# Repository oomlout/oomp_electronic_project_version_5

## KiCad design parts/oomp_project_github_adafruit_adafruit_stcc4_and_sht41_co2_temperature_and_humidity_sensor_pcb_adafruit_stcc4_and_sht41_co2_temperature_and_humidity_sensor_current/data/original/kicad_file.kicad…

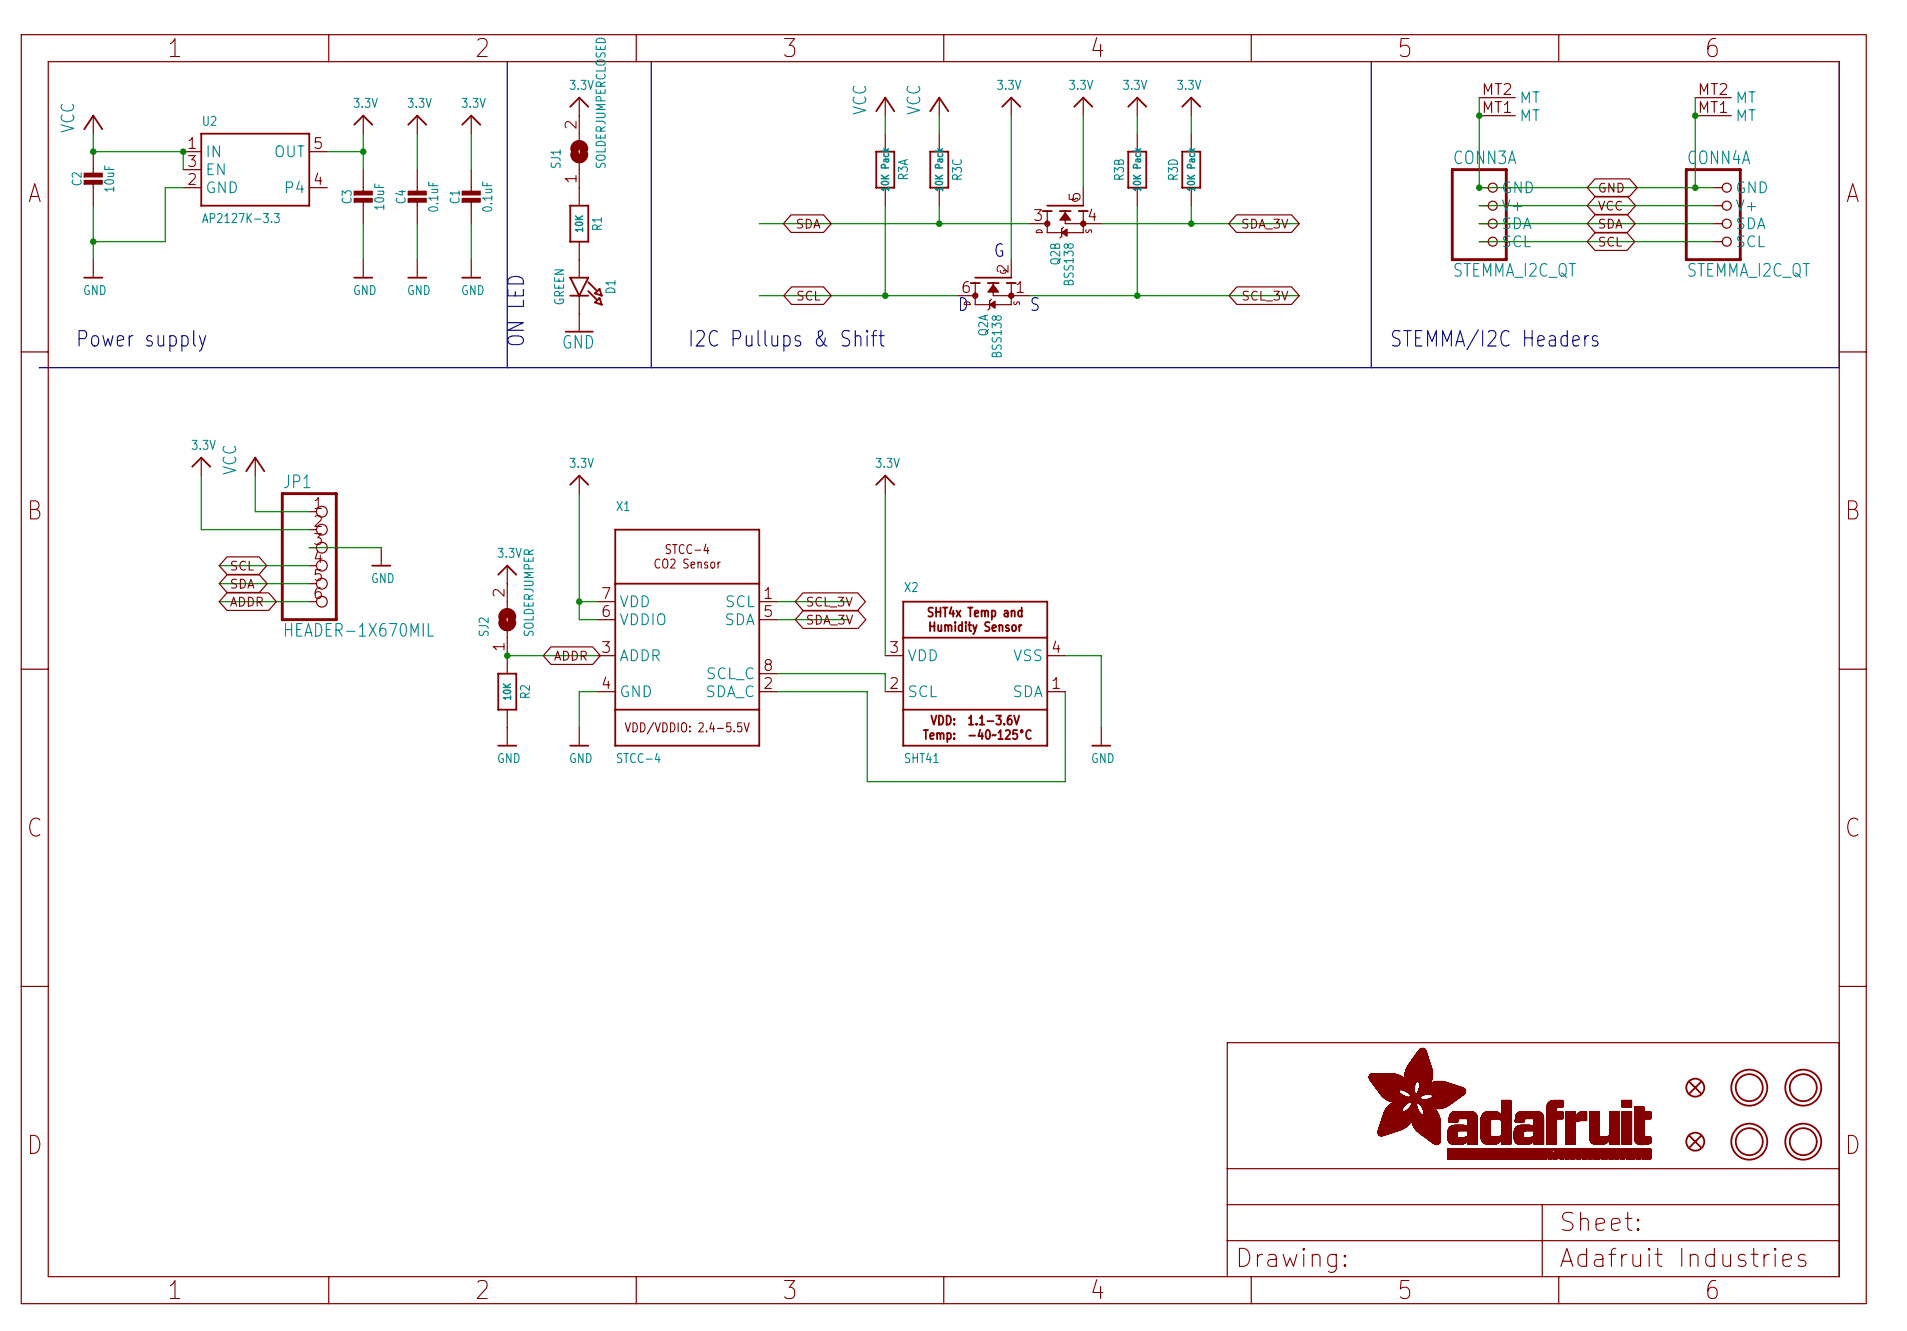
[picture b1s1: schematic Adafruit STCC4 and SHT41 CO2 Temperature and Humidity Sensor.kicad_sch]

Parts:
C1, C4: 0.1uF; 0603-NO
C2, C3: 10uF; 0805-NO
CONN3, CONN4: STEMMA_I2C_QT; JST_SH4; LCSC C2845363
D1: GREEN; CHIPLED_0603_NOOUTLINE
FID3, FID4: FIDUCIAL_0.5MM
JP1: HEADER-1X670MIL; 1X06_ROUND_70
Q2: BSS138; SOT363; JLC_ROTATION 270
R1, R2: 10K; 0603-NO
R3: 10K Pack; RESPACK_4X0603
SJ1: SOLDERJUMPERCLOSED; SOLDERJUMPER_CLOSEDWIRE
SJ2: SOLDERJUMPER; SOLDERJUMPER_ARROW_NOPASTE
U2: AP2127K-3.3; SOT23-5; JLC_ROTATION 270
U$1, U$17, U$19, U$21: MOUNTINGHOLE2.5; MOUNTINGHOLE_2.5_PLATED
X1: STCC-4; STCC4
X2: SHT41; SHT4X

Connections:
3.3V: C1.1, C3.1, C4.1, JP1.2, Q2.2 (G), Q2.5 (G), R3.2 (1), R3.4 (1), SJ1.2, SJ2.2, U2.5 (OUT), X1.6 (VDDIO), X1.7 (VDD), X2.3 (VDD)
ADDR: JP1.6, R2.1, SJ2.1, X1.3 (ADDR)
GND: C1.2, C2.2, C3.2, C4.2, CONN3.1 (GND), CONN3.MT1 (MT), CONN3.MT2 (MT), CONN4.1 (GND), CONN4.MT1 (MT), CONN4.MT2 (MT), D1.C, JP1.3, R2.2, U2.2 (GND), X1.4 (GND), X2.4 (VSS)
unnamed: D1.A, R1.2
unnamed: R1.1, SJ1.1
unnamed: X1.8 (SCL_C), X2.2 (SCL)
unnamed: X1.2 (SDA_C), X2.1 (SDA)
SCL: CONN3.4 (SCL), CONN4.4 (SCL), JP1.4, Q2.6 (D), R3.8 (2)
SCL_3V: Q2.1 (S), R3.7 (2), X1.1 (SCL)
SDA: CONN3.3 (SDA), CONN4.3 (SDA), JP1.5, Q2.3 (D), R3.6 (2)
SDA_3V: Q2.4 (S), R3.5 (2), X1.5 (SDA)
VCC: C2.1, CONN3.2 (V+), CONN4.2 (V+), JP1.1, R3.1, R3.3 (1), U2.1 (IN), U2.3 (EN)

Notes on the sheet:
Power supply
I2C Pullups & Shift
STEMMA/I2C Headers
ON LED

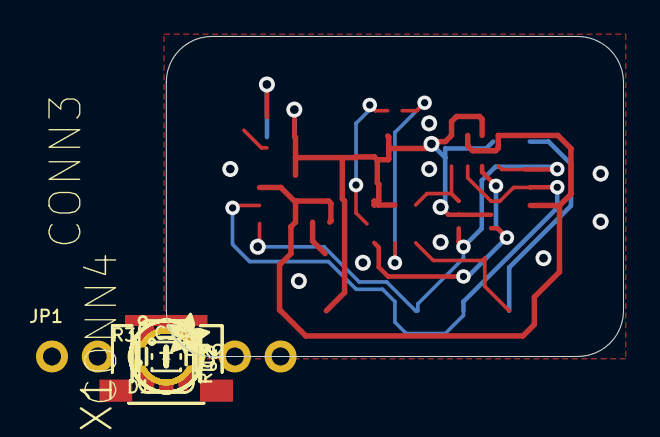
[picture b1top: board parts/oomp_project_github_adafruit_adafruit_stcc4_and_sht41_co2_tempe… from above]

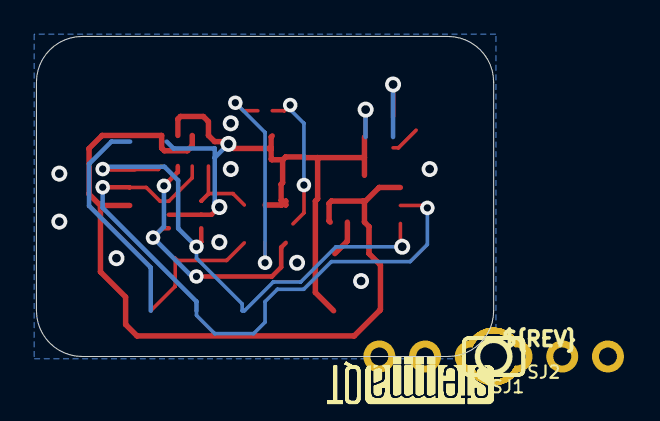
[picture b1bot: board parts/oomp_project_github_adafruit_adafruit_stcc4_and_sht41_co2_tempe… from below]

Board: 2 copper layers, 25.4 x 17.8 mm, 41 parts (10 on the bottom side), 12 nets.

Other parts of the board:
PLABEL0: PLABEL0
PLABEL1: PLABEL1
PLABEL2: PLABEL2
PLABEL3: PLABEL3
PLABEL4: PLABEL4
PLABEL5: PLABEL5
PLABEL6: PLABEL6
PLABEL7: PLABEL7
PLABEL8: PLABEL8
PLABEL9: PLABEL9
PLABEL10: PLABEL10
PLABEL11: PLABEL11
PLABEL12: PLABEL12
PLABEL13: PLABEL13
U$25: PCBFEAT-REV-040
U$28: ADAFRUIT_2.5MM
U$30, U$31: STEMMAQT

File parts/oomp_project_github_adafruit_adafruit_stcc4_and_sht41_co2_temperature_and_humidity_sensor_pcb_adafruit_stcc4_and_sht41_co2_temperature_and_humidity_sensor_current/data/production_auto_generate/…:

Comment,Designator,Footprint,LCSC Part #
,JP1,1X06_ROUND_70,C37208
,U$28,ADAFRUIT_2.5MM,
,U$25,PCBFEAT-REV-040,
,PLABEL0,PLABEL0,
,PLABEL1,PLABEL1,
,PLABEL10,PLABEL10,
,PLABEL11,PLABEL11,
,PLABEL12,PLABEL12,
,PLABEL13,PLABEL13,
,PLABEL2,PLABEL2,
,PLABEL3,PLABEL3,
,PLABEL4,PLABEL4,
,PLABEL5,PLABEL5,
,PLABEL6,PLABEL6,
,PLABEL7,PLABEL7,
,PLABEL8,PLABEL8,
,PLABEL9,PLABEL9,
,"U$30,U$31",STEMMAQT,
0.1uF,"C1,C4",0603-NO,C14663
10K,"R1,R2",0603-NO,C98220
10K Pack,R3,RESPACK_4X0603,C98220
10uF,"C2,C3",0805-NO,
AP2127K-3.3,U2,SOT23-5,
BSS138,Q2,SOT363,
GREEN,D1,CHIPLED_0603_NOOUTLINE,
SHT41,X2,SHT4X,
STCC-4,X1,STCC4,
STEMMA_I2C_QT,"CONN3,CONN4",JST_SH4,C160404

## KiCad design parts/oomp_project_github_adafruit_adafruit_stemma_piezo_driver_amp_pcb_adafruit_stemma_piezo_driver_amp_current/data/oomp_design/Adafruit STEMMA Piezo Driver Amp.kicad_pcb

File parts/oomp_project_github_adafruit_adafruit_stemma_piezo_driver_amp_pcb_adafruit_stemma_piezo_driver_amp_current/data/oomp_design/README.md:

# OOMP KiCad design copy

Open `Adafruit STEMMA Piezo Driver Amp.kicad_pro` (or the `.kicad_pcb` / `.kicad_sch`) in KiCad. Local OOMP libraries are under `libraries/`. Original inputs are preserved in [../original/](../original/).

Only verified unchanged installed KiCad defaults were renamed. Modified, custom, unmatched and unavailable items remain unchanged. Soldering variants are never swapped during conversion. Existing pad coordinates, nets and UUIDs are preserved.

See [conversion_report.yaml](conversion_report.yaml) for every conversion and skip. Copy this directory before editing; regeneration refuses to overwrite edited design files.

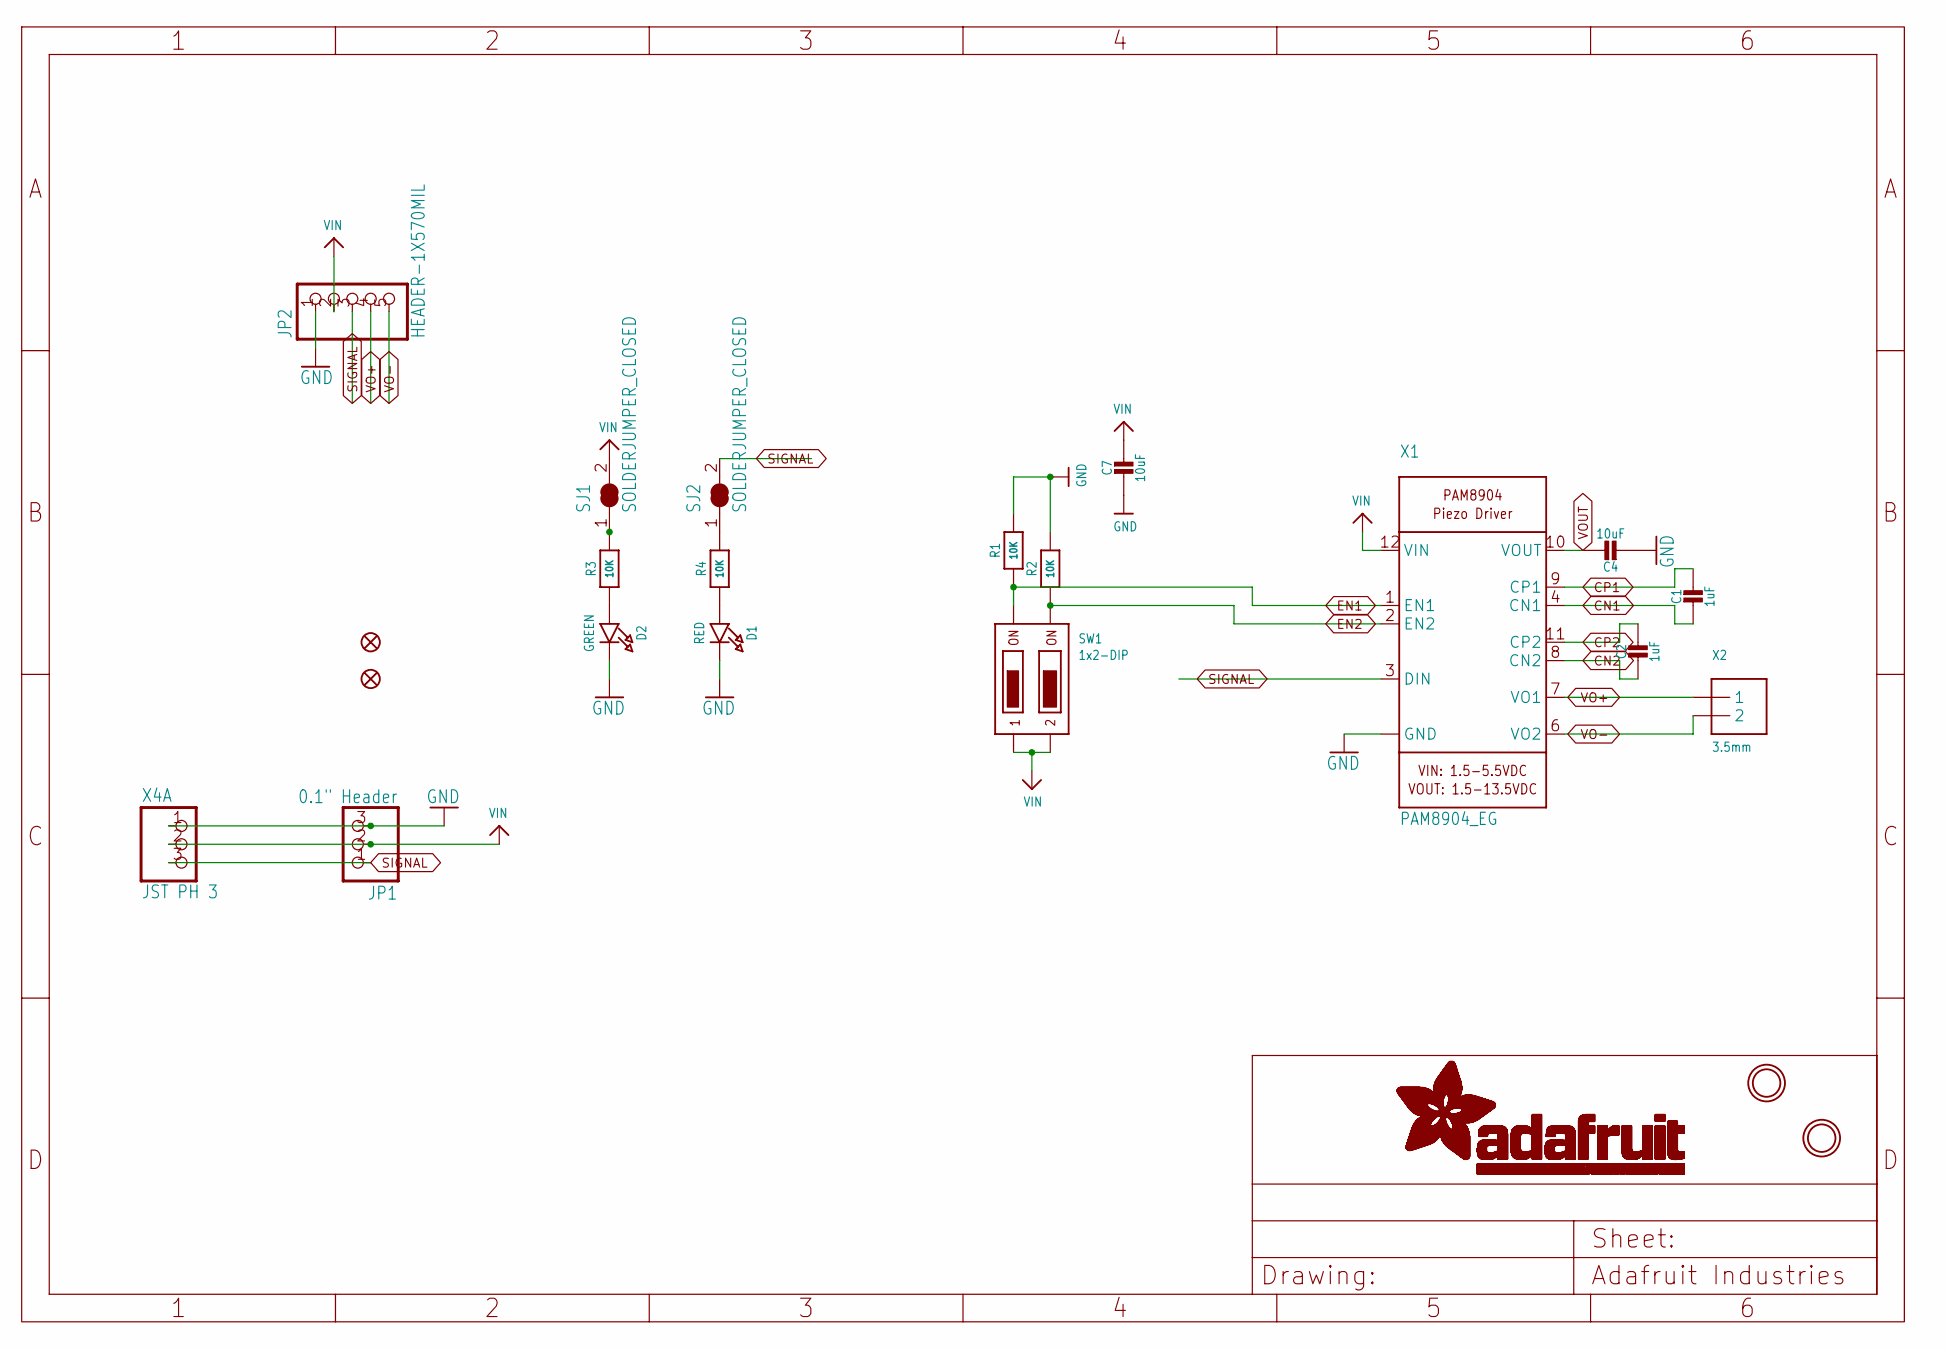
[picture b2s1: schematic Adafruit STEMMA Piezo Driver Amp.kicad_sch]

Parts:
C1, C2: 1uF; 0603-NO
C4, C7: 10uF; 0805-NO
D1: RED; CHIPLED_0603_NOOUTLINE
D2: GREEN; CHIPLED_0603_NOOUTLINE
FID2, FID3: FIDUCIAL_1MM
JP1: 0.1" Header; 1X03_OVAL
JP2: HEADER-1X570MIL; 1X05_ROUND_70
R1, R2, R3, R4: 10K; 0603-NO
SJ1, SJ2: SOLDERJUMPER_CLOSED; SOLDERJUMPER_CLOSEDWIRE
SW1: 1x2-DIP; DIPSWITCH_2PIN
U$1, U$8: MOUNTINGHOLE2.5; MOUNTINGHOLE_2.5_PLATED
X1: PAM8904_EG; QFN12-2MM
X2: 3.5mm; TERMBLOCK_1X2-3.5MM
X4: JST PH 3; JSTPH3

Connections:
CN1: C1.2, X1.4 (CN1)
CN2: C2.2, X1.8 (CN2)
CP1: C1.1, X1.9 (CP1)
CP2: C2.1, X1.11 (CP2)
EN1: R1.1, SW1.1ON, X1.1 (EN1)
EN2: R2.1, SW1.2ON, X1.2 (EN2)
GND: C4.2, C7.2, D1.C, D2.C, JP1.3, JP2.1, R1.2, R2.2, X1.5 (GND), X1.MT (GND), X4.1
unnamed: R3.2, SJ1.1
unnamed: D1.A, R4.1
unnamed: R4.2, SJ2.1
unnamed: D2.A, R3.1
SIGNAL: JP1.1, JP2.3, SJ2.2, X1.3 (DIN), X4.3
VIN: C7.1, JP1.2, JP2.2, SJ1.2, SW1.1OFF, SW1.2OFF, X1.12 (VIN), X4.2
VO+: JP2.4, X1.7 (VO1), X2.1
VO-: JP2.5, X1.6 (VO2), X2.2
VOUT: C4.1, X1.10 (VOUT)

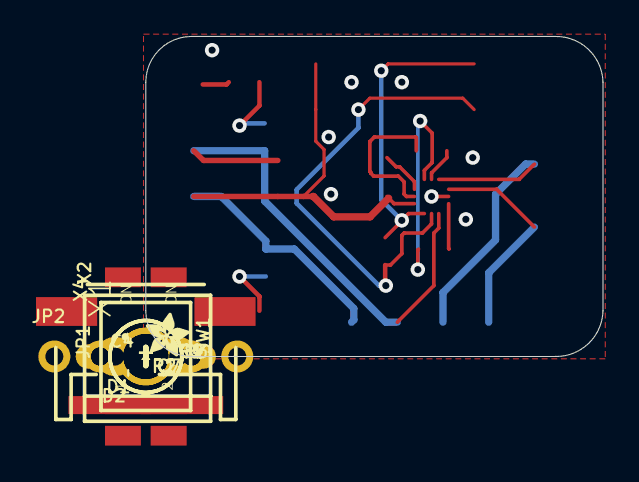
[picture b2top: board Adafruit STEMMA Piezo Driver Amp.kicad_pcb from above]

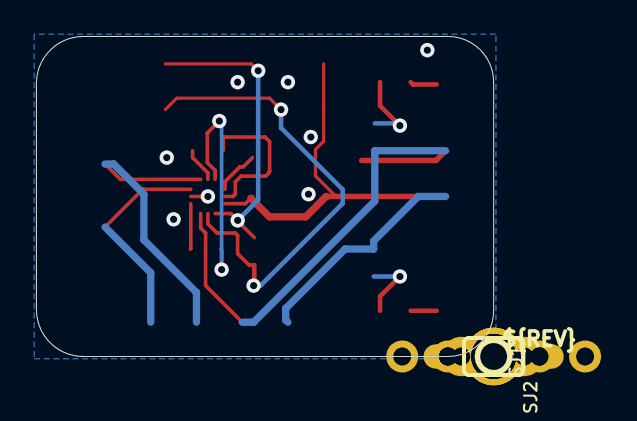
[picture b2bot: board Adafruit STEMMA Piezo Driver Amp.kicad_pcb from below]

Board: 16 copper layers, 25.4 x 17.8 mm, 38 parts (11 on the bottom side), 16 nets.

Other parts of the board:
PLABEL0: PLABEL0
PLABEL7: PLABEL7
PLABEL8: PLABEL8
PLABEL10: PLABEL10
PLABEL11: PLABEL11
PLABEL12: PLABEL12
PLABEL13: PLABEL13
PLABEL14: PLABEL14
PLABEL15: PLABEL15
PLABEL16: PLABEL16
PLABEL17: PLABEL17
PLABEL18: PLABEL18
PLABEL19: PLABEL19
PLABEL20: PLABEL20
U$5: PCBFEAT-REV-040
U$19: ADAFRUIT_2.5MM

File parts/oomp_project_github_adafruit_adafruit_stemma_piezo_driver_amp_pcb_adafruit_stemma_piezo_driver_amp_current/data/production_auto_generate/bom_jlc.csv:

Comment,Designator,Footprint,LCSC Part #
,JP2,Adafruit STEMMA Piezo Driver Amp-import-fps:1X05_ROUND_70,C42431835
,U$19,Adafruit STEMMA Piezo Driver Amp-import-fps:ADAFRUIT_2.5MM,
,U$5,Adafruit STEMMA Piezo Driver Amp-import-fps:PCBFEAT-REV-040,
,PLABEL0,Adafruit STEMMA Piezo Driver Amp-import-fps:PLABEL0,
,PLABEL10,Adafruit STEMMA Piezo Driver Amp-import-fps:PLABEL10,
,PLABEL11,Adafruit STEMMA Piezo Driver Amp-import-fps:PLABEL11,
,PLABEL12,Adafruit STEMMA Piezo Driver Amp-import-fps:PLABEL12,
,PLABEL13,Adafruit STEMMA Piezo Driver Amp-import-fps:PLABEL13,
,PLABEL14,Adafruit STEMMA Piezo Driver Amp-import-fps:PLABEL14,
,PLABEL15,Adafruit STEMMA Piezo Driver Amp-import-fps:PLABEL15,
,PLABEL16,Adafruit STEMMA Piezo Driver Amp-import-fps:PLABEL16,
,PLABEL17,Adafruit STEMMA Piezo Driver Amp-import-fps:PLABEL17,
,PLABEL18,Adafruit STEMMA Piezo Driver Amp-import-fps:PLABEL18,
,PLABEL19,Adafruit STEMMA Piezo Driver Amp-import-fps:PLABEL19,
,PLABEL20,Adafruit STEMMA Piezo Driver Amp-import-fps:PLABEL20,
,PLABEL7,Adafruit STEMMA Piezo Driver Amp-import-fps:PLABEL7,
,PLABEL8,Adafruit STEMMA Piezo Driver Amp-import-fps:PLABEL8,
"0.1"" Header",JP1,Adafruit STEMMA Piezo Driver Amp-import-fps:1X03_OVAL,C49257
10K,"R1,R2,R3,R4",Adafruit STEMMA Piezo Driver Amp-import-fps:0603-NO,C98220
10uF,"C4,C7",Adafruit STEMMA Piezo Driver Amp-import-fps:0805-NO,
1uF,"C1,C2",Adafruit STEMMA Piezo Driver Amp-import-fps:0603-NO,C5673
1x2-DIP,SW1,Adafruit STEMMA Piezo Driver Amp-import-fps:DIPSWITCH_2PIN,
3.5mm,X2,Adafruit STEMMA Piezo Driver Amp-import-fps:TERMBLOCK_1X2-3.5MM,
GREEN,D2,Adafruit STEMMA Piezo Driver Amp-import-fps:CHIPLED_0603_NOOUTLINE,
JST PH 3,X4,Adafruit STEMMA Piezo Driver Amp-import-fps:JSTPH3,
PAM8904_EG,X1,Adafruit STEMMA Piezo Driver Amp-import-fps:QFN12-2MM,
RED,D1,Adafruit STEMMA Piezo Driver Amp-import-fps:CHIPLED_0603_NOOUTLINE,

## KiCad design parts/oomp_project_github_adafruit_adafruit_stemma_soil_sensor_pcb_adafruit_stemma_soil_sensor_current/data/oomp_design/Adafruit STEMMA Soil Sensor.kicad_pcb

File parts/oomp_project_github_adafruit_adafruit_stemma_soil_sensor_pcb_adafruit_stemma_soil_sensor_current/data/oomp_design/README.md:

# OOMP KiCad design copy

Open `Adafruit STEMMA Soil Sensor.kicad_pro` (or the `.kicad_pcb` / `.kicad_sch`) in KiCad. Local OOMP libraries are under `libraries/`. Original inputs are preserved in [../original/](../original/).

Only verified unchanged installed KiCad defaults were renamed. Modified, custom, unmatched and unavailable items remain unchanged. Soldering variants are never swapped during conversion. Existing pad coordinates, nets and UUIDs are preserved.

See [conversion_report.yaml](conversion_report.yaml) for every conversion and skip. Copy this directory before editing; regeneration refuses to overwrite edited design files.

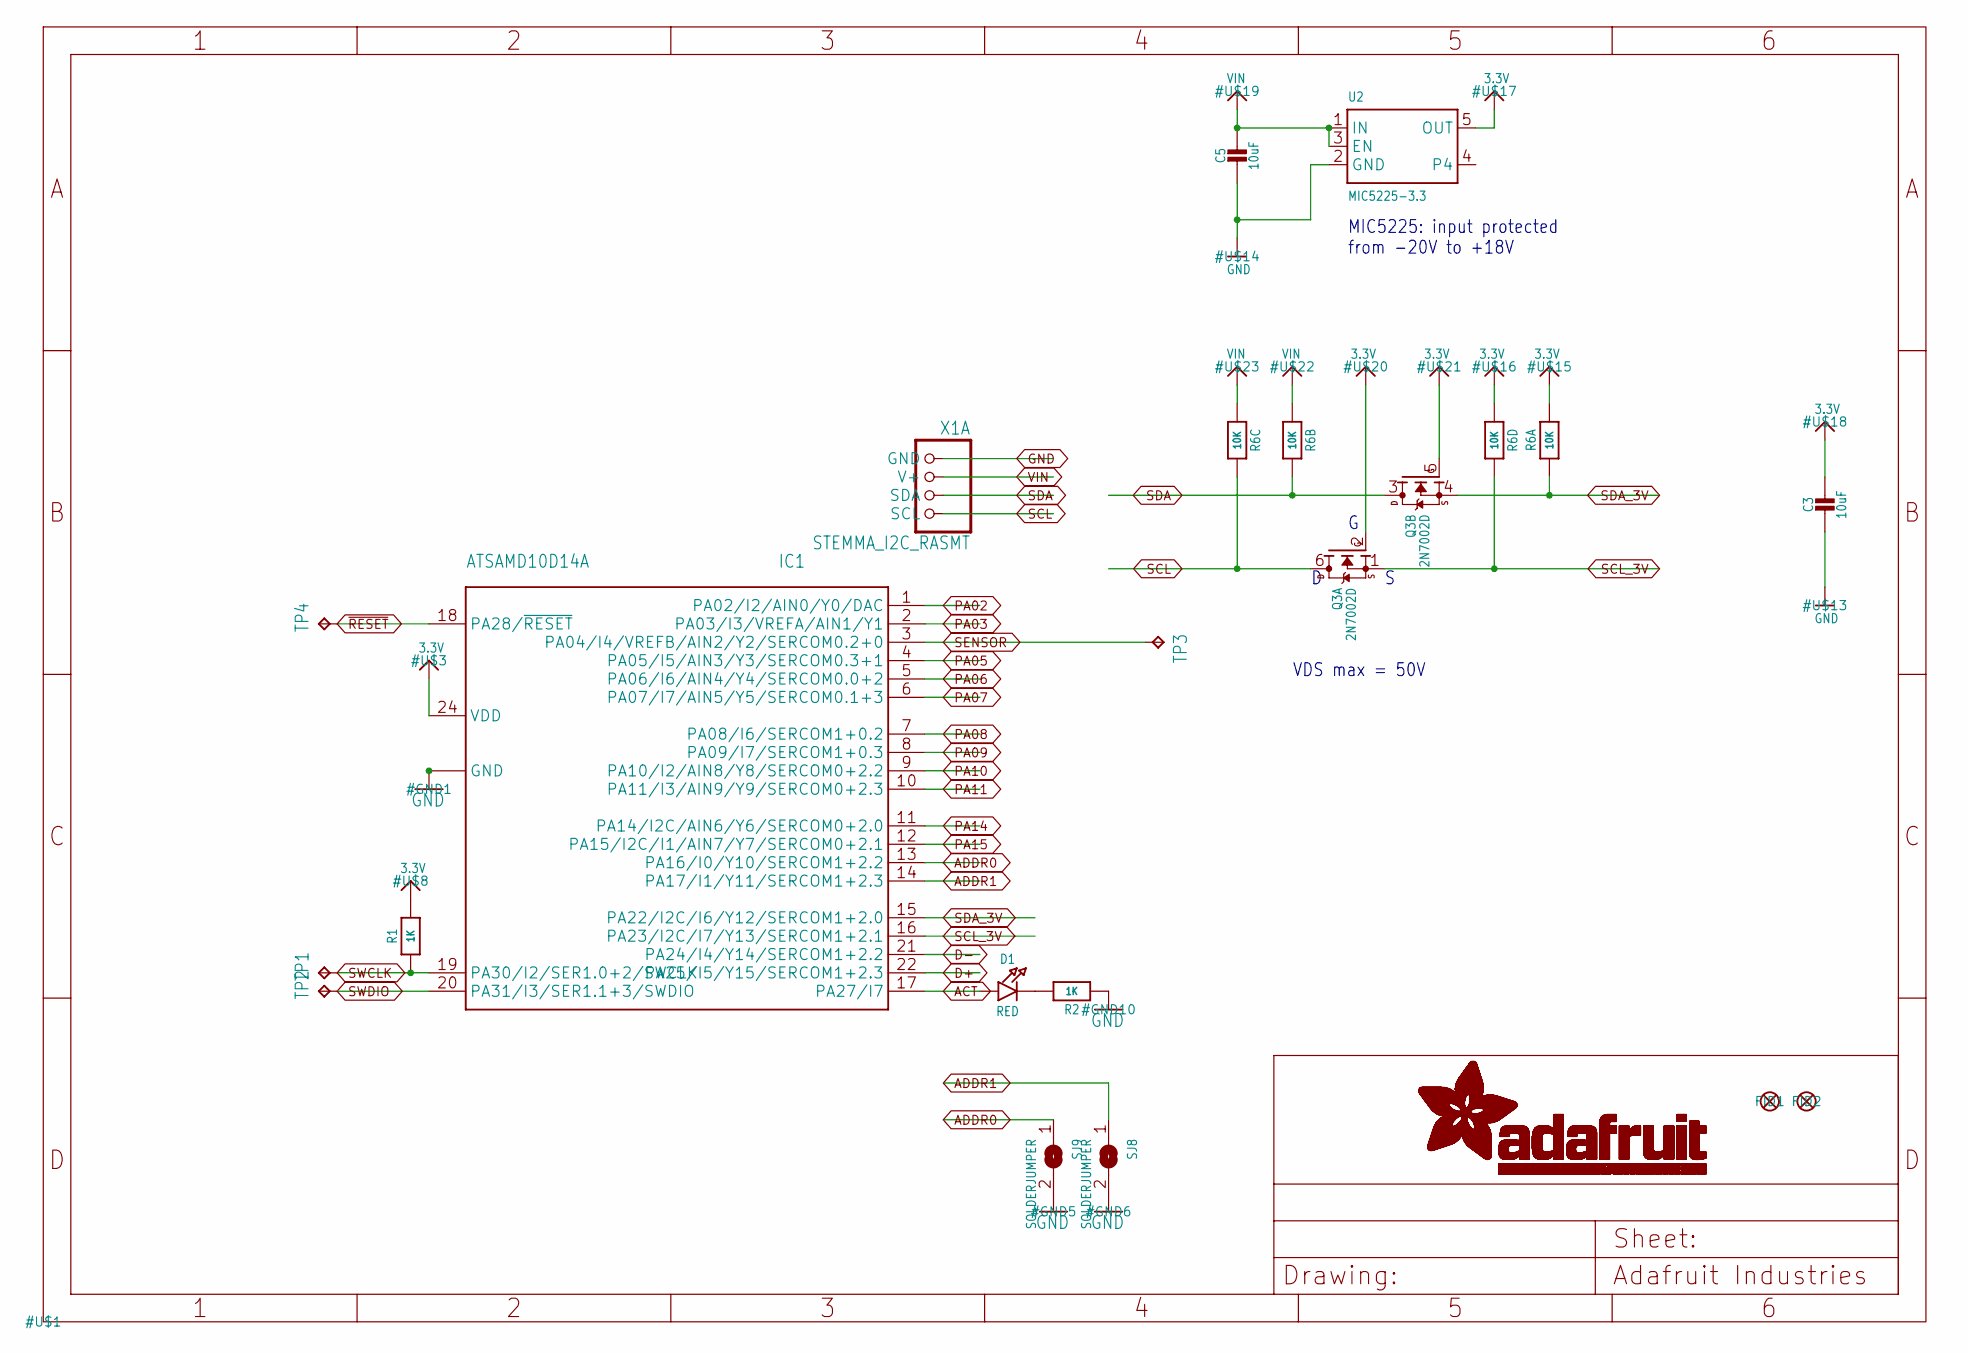
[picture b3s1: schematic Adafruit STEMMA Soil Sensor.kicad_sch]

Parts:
C3, C5: 10uF; 0805-NO
D1: RED; CHIPLED_0805_NOOUTLINE
FID1, FID2: FIDUCIAL_1MM
IC1: ATSAMD10D14A; QFN24_4MM
Q3: 2N7002D; SOT363
R1, R2: 1K; 0603-NO
R6: 10K; RESPACK_4X0603
SJ8, SJ9: SOLDERJUMPER; SOLDERJUMPER_ARROW_NOPASTE
TP1, TP2, TP4: TPTP15R; TP15R
TP3: TPTP10R; TP10R
U2: MIC5225-3.3; SOT23-5
X1: STEMMA_I2C_RASMT; JSTPH4

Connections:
3.3V: C3.1, IC1.24 (VDD), Q3.2 (G), Q3.5 (G), R1.2, R6.1, R6.5 (2), U2.5 (OUT)
ACT: D1.A, IC1.17 (PA27/I7)
ADDR0: IC1.13 (PA16/I0/Y10/SERCOM1+2.2), SJ9.1
ADDR1: IC1.14 (PA17/I1/Y11/SERCOM1+2.3), SJ8.1
D+: IC1.22 (PA25/I5/Y15/SERCOM1+2.3)
D-: IC1.21 (PA24/I4/Y14/SERCOM1+2.2)
GND: C3.2, C5.2, IC1.23 (GND), IC1.THERM (GND), R2.1, SJ8.2, SJ9.2, U2.2 (GND), X1.1 (GND)
unnamed: D1.C, R2.2
PA02: IC1.1 (PA02/I2/AIN0/Y0/DAC)
PA03: IC1.2 (PA03/I3/VREFA/AIN1/Y1)
PA05: IC1.4 (PA05/I5/AIN3/Y3/SERCOM0.3+1)
PA06: IC1.5 (PA06/I6/AIN4/Y4/SERCOM0.0+2)
PA07: IC1.6 (PA07/I7/AIN5/Y5/SERCOM0.1+3)
PA08: IC1.7 (PA08/I6/SERCOM1+0.2)
PA09: IC1.8 (PA09/I7/SERCOM1+0.3)
PA10: IC1.9 (PA10/I2/AIN8/Y8/SERCOM0+2.2)
PA11: IC1.10 (PA11/I3/AIN9/Y9/SERCOM0+2.3)
PA14: IC1.11 (PA14/I2C/AIN6/Y6/SERCOM0+2.0)
PA15: IC1.12 (PA15/I2C/I1/AIN7/Y7/SERCOM0+2.1)
SCL: Q3.6 (D), R6.6 (2), X1.4 (SCL)
SCL_3V: IC1.16 (PA23/I2C/I7/Y13/SERCOM1+2.1), Q3.1 (S), R6.4 (1)
SDA: Q3.3 (D), R6.7 (2), X1.3 (SDA)
SDA_3V: IC1.15 (PA22/I2C/I6/Y12/SERCOM1+2.0), Q3.4 (S), R6.8 (2)
SENSOR: IC1.3 (PA04/I4/VREFB/AIN2/Y2/SERCOM0.2+0), TP3.TP
SWCLK: IC1.19 (PA30/I2/SER1.0+2/SWCLK), R1.1, TP1.TP
SWDIO: IC1.20 (PA31/I3/SER1.1+3/SWDIO), TP2.TP
VIN: C5.1, R6.2 (1), R6.3 (1), U2.1 (IN), U2.3 (EN), X1.2 (V+)
~RESET: IC1.18 (PA28/~RESET), TP4.TP

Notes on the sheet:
VDS max = 50V
MIC5225: input protected from -20V to +18V

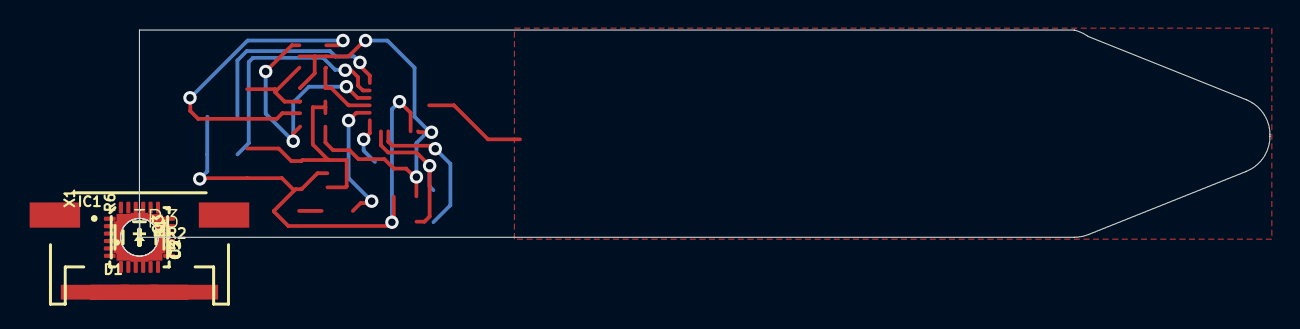
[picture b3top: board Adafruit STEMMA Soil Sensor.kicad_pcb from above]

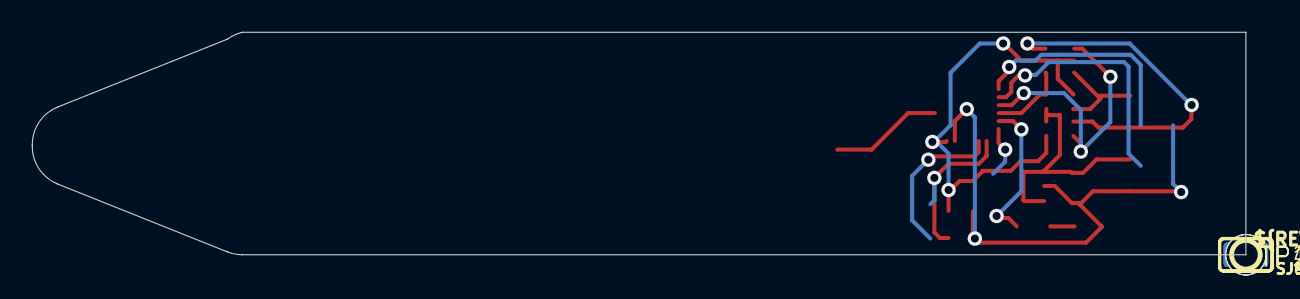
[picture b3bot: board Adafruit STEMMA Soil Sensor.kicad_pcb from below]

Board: 2 copper layers, 76.2 x 14.0 mm, 23 parts (7 on the bottom side), 15 nets.

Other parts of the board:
U$4: STEMMA_SOIL_BOT
U$5: STEMMA_SOIL_TOP
U$12: PCBFEAT-REV-040
UNK_HOLE_0: dummyfp0
UNK_HOLE_1: dummyfp1

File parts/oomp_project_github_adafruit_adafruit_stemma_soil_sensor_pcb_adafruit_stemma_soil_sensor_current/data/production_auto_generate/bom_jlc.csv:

Comment,Designator,Footprint,LCSC Part #
,U$12,Adafruit STEMMA Soil Sensor-import-fps:PCBFEAT-REV-040,
,U$4,Adafruit STEMMA Soil Sensor-import-fps:STEMMA_SOIL_BOT,
,U$5,Adafruit STEMMA Soil Sensor-import-fps:STEMMA_SOIL_TOP,
10K,R6,Adafruit STEMMA Soil Sensor-import-fps:RESPACK_4X0603,C98220
10uF,"C3,C5",Adafruit STEMMA Soil Sensor-import-fps:0805-NO,
1K,"R1,R2",Adafruit STEMMA Soil Sensor-import-fps:0603-NO,C2907002
2N7002D,Q3,Adafruit STEMMA Soil Sensor-import-fps:SOT363,
ATSAMD10D14A,IC1,Adafruit STEMMA Soil Sensor-import-fps:QFN24_4MM,
MIC5225-3.3,U2,Adafruit STEMMA Soil Sensor-import-fps:SOT23-5,
RED,D1,Adafruit STEMMA Soil Sensor-import-fps:CHIPLED_0805_NOOUTLINE,
STEMMA_I2C_RASMT,X1,Adafruit STEMMA Soil Sensor-import-fps:JSTPH4,
TPTP10R,TP3,Adafruit STEMMA Soil Sensor-import-fps:TP10R,
TPTP15R,"TP1,TP2,TP4",Adafruit STEMMA Soil Sensor-import-fps:TP15R,

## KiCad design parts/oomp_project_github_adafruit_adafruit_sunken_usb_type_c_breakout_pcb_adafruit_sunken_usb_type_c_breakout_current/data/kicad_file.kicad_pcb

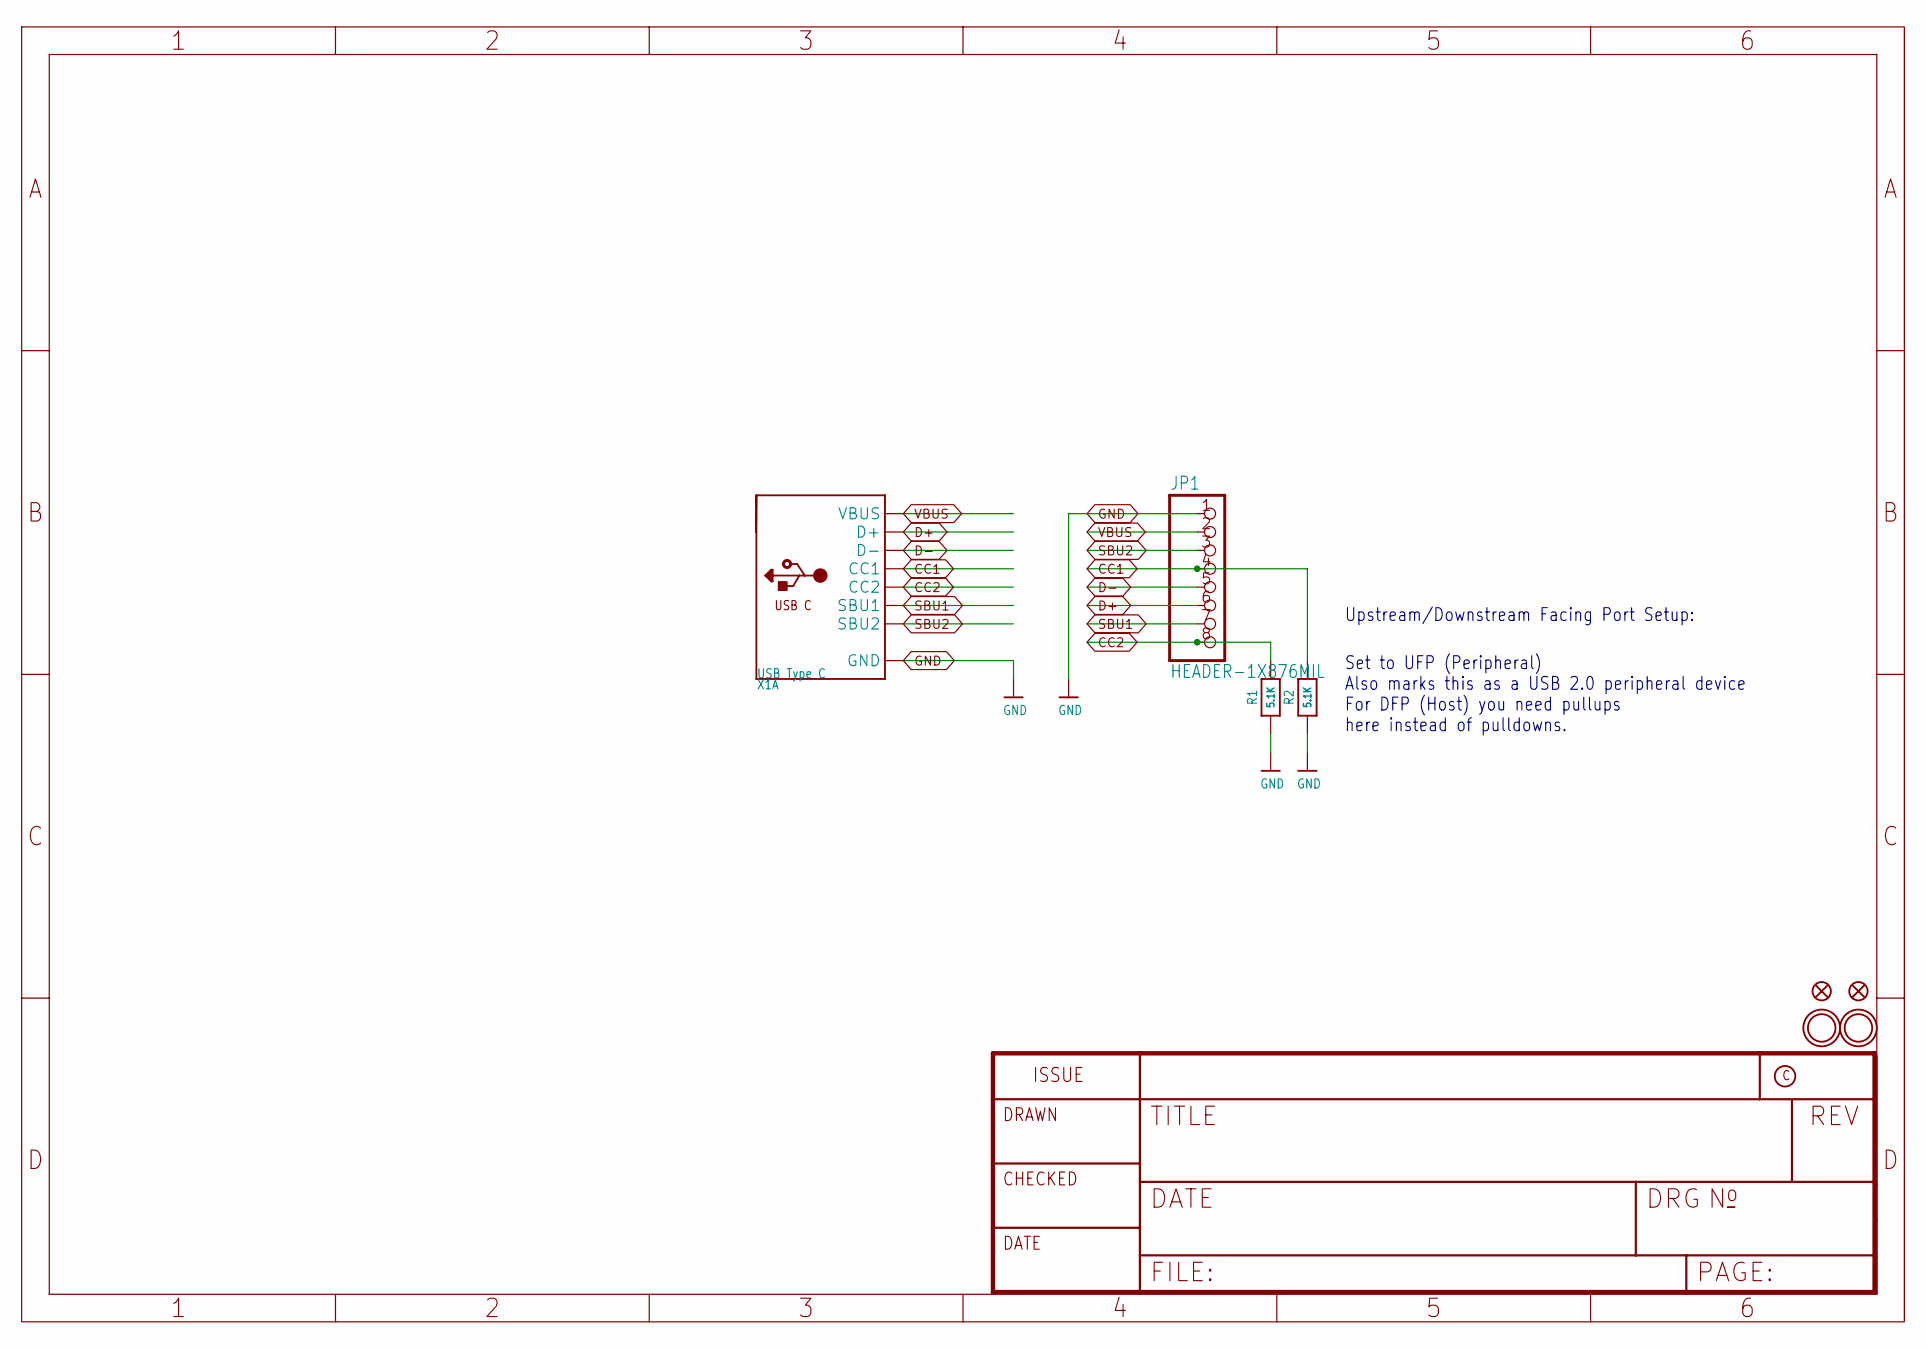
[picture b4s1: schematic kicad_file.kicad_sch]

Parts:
FID1, FID2: FIDUCIAL_0.5MM
JP1: HEADER-1X876MIL; 1X08_ROUND_76
R1, R2: 5.1K; 0603-NO
U$1, U$2: MOUNTINGHOLE2.5; MOUNTINGHOLE_2.5_PLATED
X1: USB Type C; USB_C_SINK

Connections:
CC1: JP1.4, R2.2, X1.A5 (CC1)
CC2: JP1.8, R1.2, X1.B5 (CC2)
D+: JP1.6, X1.A6 (D+), X1.B6 (D+)
D-: JP1.5, X1.A7 (D-), X1.B7 (D-)
GND: JP1.1, R1.1, R2.1, X1.A1B12 (GND), X1.B1A12 (GND)
SBU1: JP1.7, X1.A8 (SBU1)
SBU2: JP1.3, X1.B8 (SBU2)
VBUS: JP1.2, X1.A4B9 (VBUS), X1.B4A9 (VBUS)

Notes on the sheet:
Set to UFP (Peripheral) Also marks this as a USB 2.0 peripheral device For DFP (Host) you need pullups here instead of pulldowns.
Upstream/Downstream Facing Port Setup:

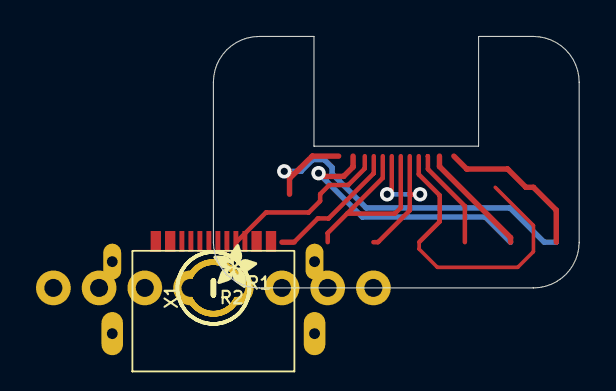
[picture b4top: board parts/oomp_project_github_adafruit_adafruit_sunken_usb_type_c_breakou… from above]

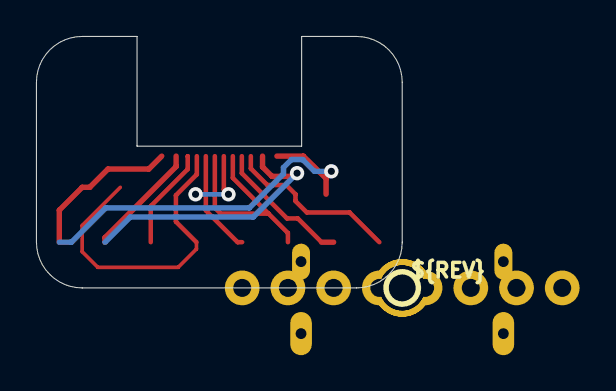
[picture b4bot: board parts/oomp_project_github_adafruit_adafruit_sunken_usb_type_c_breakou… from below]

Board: 2 copper layers, 20.3 x 14.0 mm, 21 parts (3 on the bottom side), 8 nets.

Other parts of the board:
PLABEL0: PLABEL0
PLABEL1: PLABEL1
PLABEL2: PLABEL2
PLABEL3: PLABEL3
PLABEL4: PLABEL4
PLABEL5: PLABEL5
PLABEL6: PLABEL6
PLABEL7: PLABEL7
PLABEL8: PLABEL8
PLABEL9: PLABEL9
PLABEL10: PLABEL10
U$3: ADAFRUIT_2.5MM
U$8: PCBFEAT-REV-040
